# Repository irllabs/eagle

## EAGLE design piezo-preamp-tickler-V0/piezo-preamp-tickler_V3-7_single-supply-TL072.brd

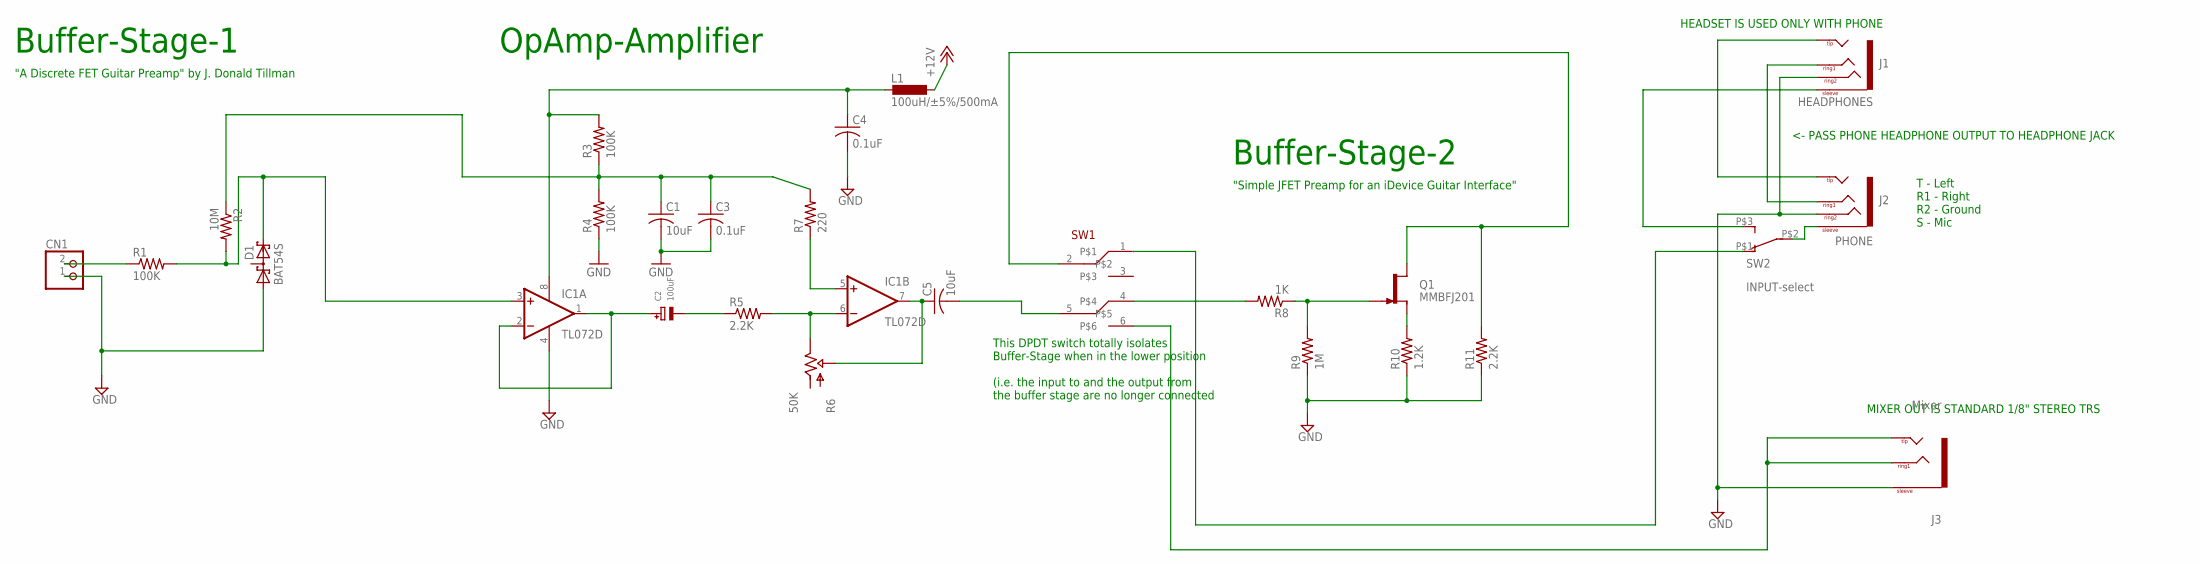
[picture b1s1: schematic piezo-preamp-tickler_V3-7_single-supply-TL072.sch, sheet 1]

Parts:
C1: 10uF; C0805K
C2: 100uF; EIA7343-31/D-R
C3, C4: 0.1uF; C0805K
C5: 10uF; C0805
CN1: JST_2PIN-THM; JST-PH-2-THM
D1: BAT54S; SOT23
IC1: TL072D; SO08
J1: HEADPHONES; TRRS_SJ-43514-SMT-TR
J2: PHONE; TRRS_SJ-43514-SMT-TR
J3: Mixer; TRS_SJ-3524-SMT
L1: 100uH/±5%/500mA; L3225M
Q1: MMBFJ201; SOT23-3
R1, R3, R4: 100K; R0603
R2: 10M; R0603
R5, R11: 2.2K; R0603
R6: 50K; THUMBPOT14MM
R7: 220; R0603
R8: 1K; R0603
R9: 1M; R0603
R10: 1.2K; R0603
SW1: SWITCH_DPDT; SWITCH_DPDT_CL-SB-22B
SW2: INPUT-select; SWITCH_SPDT_CL-SB-12B

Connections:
+12V: L1.1; also elsewhere on the board
GND: C1.2, C3.2, C4.2, CN1.1 (2), D1.1 (A1), IC1.4 (V-), J1.RING2, J2.RING2, J3.1 (SLEEVE), R4.1, R9.1, R10.1, R11.1; also elsewhere on the board
unnamed: D1.2 (C2), IC1.3 (+IN), R1.2, R2.2
unnamed: CN1.2 (1), R1.1
unnamed: Q1.2 (S), R10.2
unnamed: J1.EARTH (SLEEVE), SW2.P$3 (3)
unnamed: IC1.5 (+IN), R7.1
unnamed: C5.1, C5.+, IC1.7 (OUT), R6.P$2 (WIPER)
unnamed: IC1.6 (-IN), R5.2, R6.P$3 (OUT)
unnamed: C4.1, IC1.8 (V+), L1.2, R3.2
unnamed: C1.1, C3.1, R2.1, R3.1, R4.2, R7.2
unnamed: Q1.3 (G), R8.1, R9.2
unnamed: R8.2, SW1.4
unnamed: J3.2 (TIP), J3.3 (RING1), J3.4 (TIP), SW1.6
unnamed: J1.RING1, J2.RING1
unnamed: C2.-, R5.1
unnamed: C5.2, C5.-, SW1.5
unnamed: J2.EARTH (SLEEVE), SW2.P$2 (2)
unnamed: SW1.1, SW2.P$1 (1)
unnamed: C2.+, IC1.1 (OUT), IC1.2 (-IN)
unnamed: J1.TIP, J2.TIP
SELECT: Q1.1 (D), R11.2, SW1.2

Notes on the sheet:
Buffer-Stage-1
OpAmp-Amplifier
Buffer-Stage-2
"A Discrete FET Guitar Preamp" by J. Donald Tillman
"Simple JFET Preamp for an iDevice Guitar Interface"
T - Left R1 - Right R2 - Ground S - Mic
HEADSET IS USED ONLY WITH PHONE
MIXER OUT IS STANDARD 1/8" STEREO TRS
<- PASS PHONE HEADPHONE OUTPUT TO HEADPHONE JACK
This DPDT switch totally isolates Buffer-Stage when in the lower position (i.e. the input to and the output from the buffer stage are no longer connected

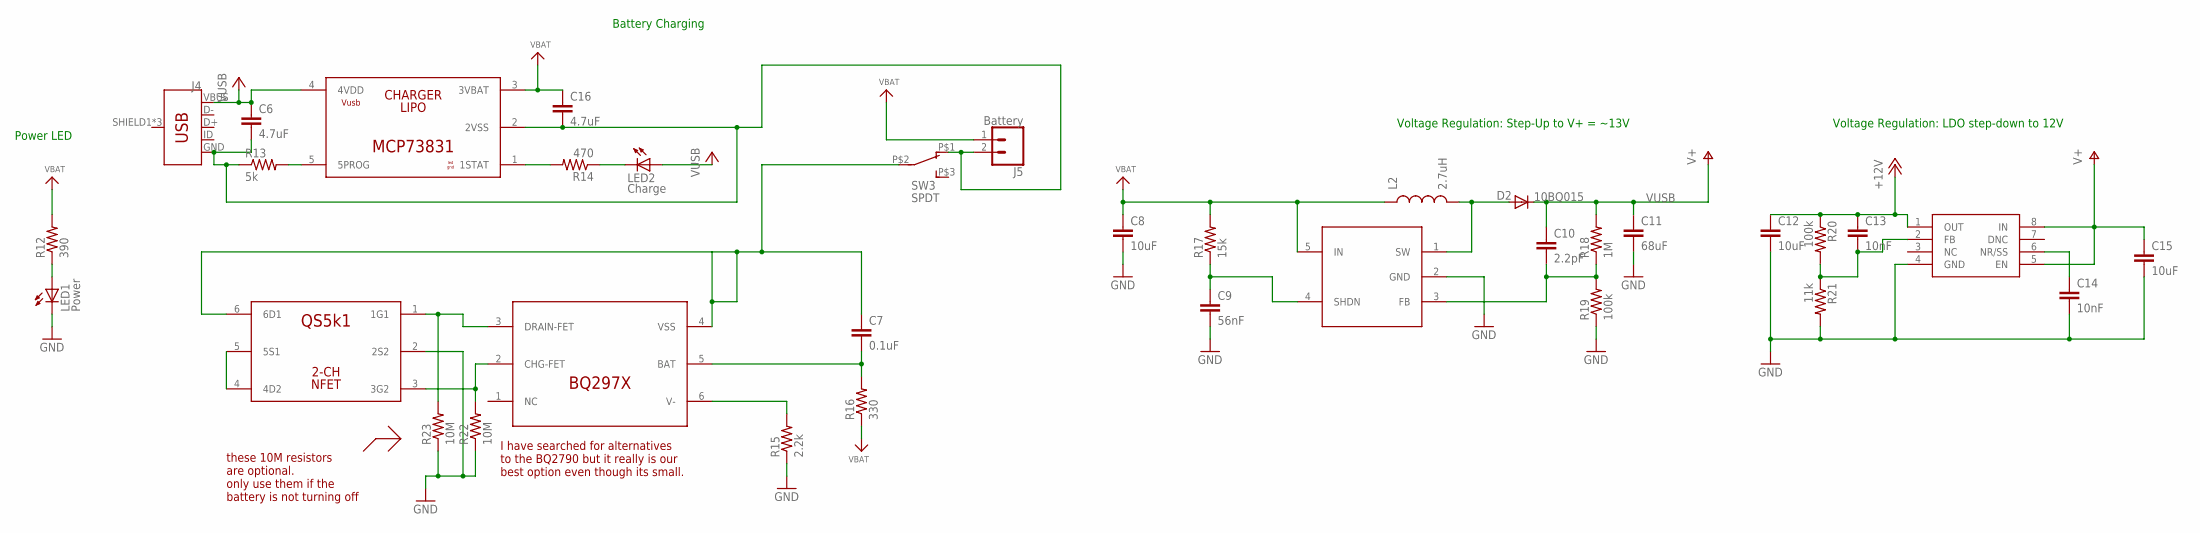
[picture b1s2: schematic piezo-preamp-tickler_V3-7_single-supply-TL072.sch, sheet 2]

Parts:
C6, C16: 4.7uF; C0603
C7: 0.1uF; C0603
C8, C12, C15: 10uF; C0603
C9: 56nF; C0603
C10: 2.2pF; C0603
C11: 68uF; C1206
C13, C14: 10nF; C0603
D2: 10BQ015; SMA-DIODE
IC2: MCP73831; SOT-23-5
IC3: QS6K1; SOT457R_PHILIPS
IC4: BQ297X; WSON-6-LONG
IC5: SC4503; SOT23-5
IC6: TPS7A49; MSOP-8
J4: USB_MICRO-BREDUCED_PASTE; USB-B-MICRO-SMD_RED_PASTE
J5: Battery; 1X02_LOCK
L2: 2.7uH; CR54
LED1: Power; LED3MM
LED2: Charge; LED3MM
R12: 390; R0603
R13: 5k; R0603
R14: 470; R0603
R15: 2.2k; R0603
R16: 330; R0603
R17: 15k; R0603
R18: 1M; R0603
R19, R20: 100k; R0603
R21: 11k; R0603
R22, R23: 10M; R0603
SW3: SPDT; SWITCH_SPDT_CL-SB-12B

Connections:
+5V: C6.1, IC2.4 (4VDD), J4.VBUS, LED2.A
+12V: C12.1, C13.1, IC6.1 (OUT), R20.1; also elsewhere on the board
BATGND: C7.1, IC3.6 (6D1), IC4.4 (VSS), SW3.P$2 (2)
GND: C8.2, C9.2, C11.2, C12.2, C14.2, C15.2, IC3.2 (2S2), IC5.2 (GND), IC6.4 (GND), LED1.K (C), R15.1, R19.1, R21.2, R22.1, R23.1; also elsewhere on the board
unnamed: LED1.A, R12.1
unnamed: IC2.5 (5PROG), R13.2
unnamed: LED2.K (C), R14.1
unnamed: IC3.4 (4D2), IC3.5 (5S1)
unnamed: IC2.1 (1STAT), R14.2
unnamed: C13.2, IC6.2 (FB), R20.2, R21.1
unnamed: IC3.1 (1G1), IC4.3 (DRAIN-FET), R23.2
unnamed: C14.1, IC6.6 (NR/SS)
unnamed: C9.1, IC5.4 (SHDN), R17.1
unnamed: C10.2, IC5.3 (FB), R18.1, R19.2
unnamed: IC3.3 (3G2), IC4.2 (CHG-FET), R22.2
unnamed: D2.A, IC5.1 (SW), L2.P$2 (2)
unnamed: IC4.6 (V-), R15.2
unnamed: C7.2, IC4.5 (BAT), R16.2
USBGND: C6.2, C16.2, IC2.2 (2VSS), J4.GND, J5.2, R13.1, SW3.P$1 (1)
VBAT: C8.1, C16.1, IC2.3 (3VBAT), IC5.5 (IN), J5.1, L2.P$1 (1), R12.2, R16.1, R17.2
VUSB: C10.1, C11.1, C15.1, D2.C, IC6.5 (EN), IC6.8 (IN), R18.2

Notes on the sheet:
Voltage Regulation: Step-Up to V+ = ~13V
Power LED
Voltage Regulation: LDO step-down to 12V
Battery Charging
I have searched for alternatives to the BQ2790 but it really is our best option even though its small.
these 10M resistors are optional. only use them if the battery is not turning off

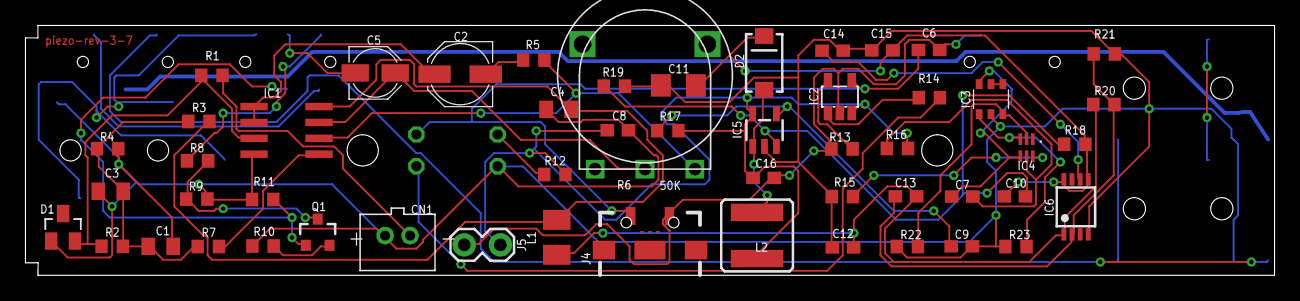
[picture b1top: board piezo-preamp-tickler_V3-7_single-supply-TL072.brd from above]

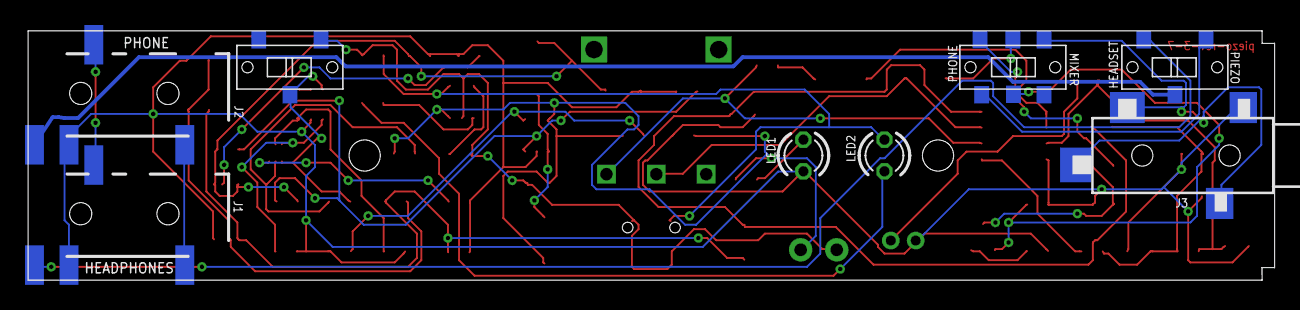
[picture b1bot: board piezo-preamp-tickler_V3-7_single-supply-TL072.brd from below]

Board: 2 copper layers, 100.0 x 20.0 mm, 61 parts (8 on the bottom side), 41 nets.

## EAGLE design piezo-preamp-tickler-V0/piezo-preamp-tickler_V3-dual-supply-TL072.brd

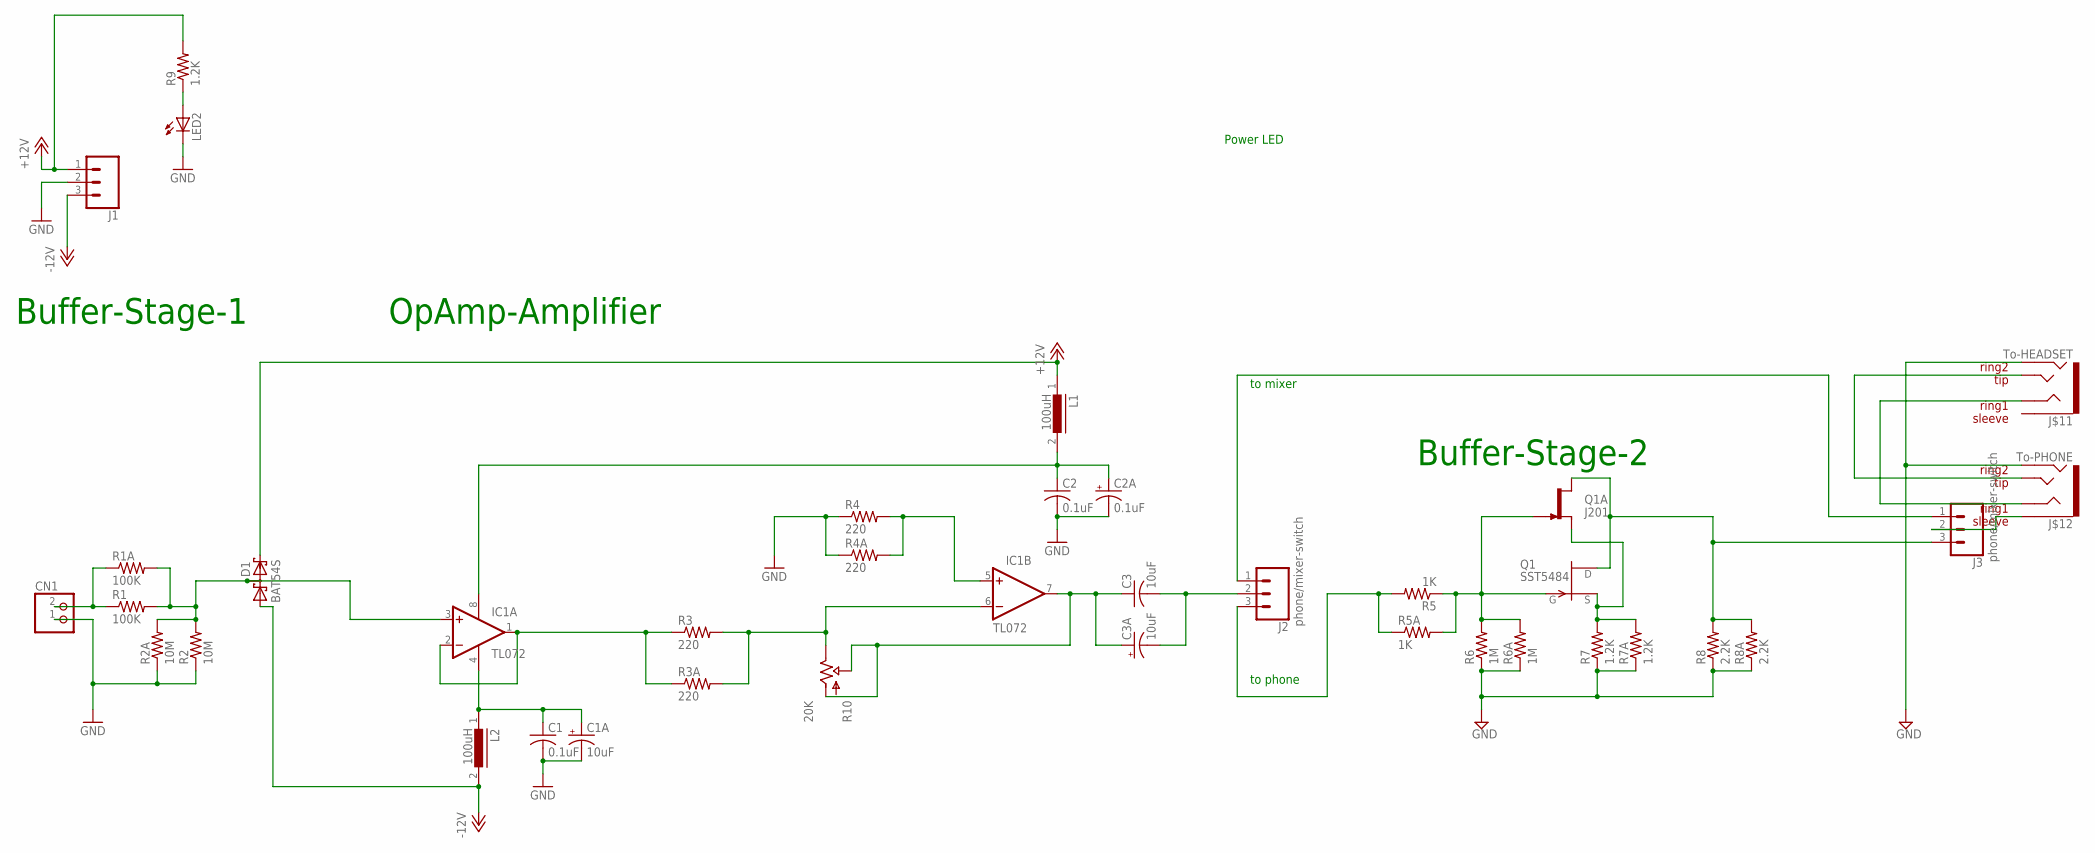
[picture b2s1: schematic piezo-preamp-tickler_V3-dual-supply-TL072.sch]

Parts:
C1, C2: 0.1uF; C0805K
C1A, C3A: 10uF; E2,5-6E
C2A: 0.1uF; E2,5-6E
C3: 10uF; C0805K
CN1: JST_2PIN-THM; JST-PH-2-THM
D1: BAT54S; SOT23
IC1: TL072; SO08
J1: CONN_03LOCK; 1X03_LOCK
J2, J3: phone/mixer-switch; 1X03_LOCK
J$11: To-HEADSET; TRRS-SJ-43514-SMT-TR
J$12: To-PHONE; TRRS-SJ-43514-SMT-TR
L1, L2: 100uH; LBC-SE
LED2: LED3MM
Q1: SST5484; SOT23
Q1A: J201; TO92-
R1: 100K; R0603
R1A: 100K; 0204V
R2: 10M; R0603
R2A: 10M; 0204V
R3, R4: 220; R0603
R3A, R4A: 220; 0204V
R5: 1K; R0603
R5A: 1K; 0204V
R6: 1M; R0603
R6A: 1M; 0204V
R7: 1.2K; R0603
R7A, R9: 1.2K; 0204V
R8: 2.2K; R0603
R8A: 2.2K; 0204V
R10: 20K; TRIMPOT-MULTI

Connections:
+12V: D1.2 (C2), J1.1, L1.1, R9.2
-12V: D1.1 (A1), J1.3, L2.2
GND: C1.2, C1A.-, C2.2, C2A.-, CN1.1 (2), J1.2, J$11.4 (RING2), J$12.4 (RING2), LED2.K (C), R2.1, R2A.1, R4.1, R4A.1, R6.1, R6A.1, R7.1, R7A.1, R8.1, R8A.1
unnamed: IC1.1 (OUT), IC1.2 (-IN), R3.1, R3A.1
unnamed: J2.3, R5.2, R5A.1
unnamed: C1.1, C1A.+, IC1.4 (V-), L2.1
unnamed: LED2.A, R9.1
unnamed: IC1.5 (+IN), R4.2, R4A.2
unnamed: IC1.6 (-IN), R3.2, R3A.2, R10.P$1 (OUT), R10.P$3 (OUT), R10.P$4 (OUT), R10.P$6 (OUT), R10.P$9 (OUT)
unnamed: C3.2, C3A.-, J2.2
unnamed: CN1.2 (1), R1.1, R1A.1
unnamed: Q1.2 (S), Q1A.2 (S), R7.2, R7A.2
unnamed: C3.1, C3A.+, IC1.7 (OUT), R10.P$10 (WIPER), R10.P$12 (WIPER), R10.P$13 (WIPER), R10.P$15 (WIPER), R10.P$16 (WIPER), R10.P$18 (WIPER), R10.P$20 (IN), R10.P$21 (IN), R10.P$22 (IN), R10.P$24 (IN), R10.P$27 (IN)
unnamed: C2.1, C2A.+, IC1.8 (V+), L1.2
unnamed: D1.3 (C1A2), IC1.3 (+IN), R1.2, R1A.2, R2.2, R2A.2
unnamed: Q1.3 (G), Q1A.1 (G), R5.1, R5A.2, R6.2, R6A.2
unnamed: J2.1, J3.1
unnamed: J$11.2 (TIP), J$12.2 (TIP)
unnamed: J$11.3 (RING1), J$12.3 (RING1)
unnamed: J3.2, J$12.1 (EARTH)
SELECT1: J3.3, Q1.1 (D), Q1A.3 (D), R8.2, R8A.2

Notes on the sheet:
Buffer-Stage-1
OpAmp-Amplifier
Buffer-Stage-2
to mixer
to phone
Power LED

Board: 2 copper layers, 37 parts (0 on the bottom side), 21 nets, no tracks yet.

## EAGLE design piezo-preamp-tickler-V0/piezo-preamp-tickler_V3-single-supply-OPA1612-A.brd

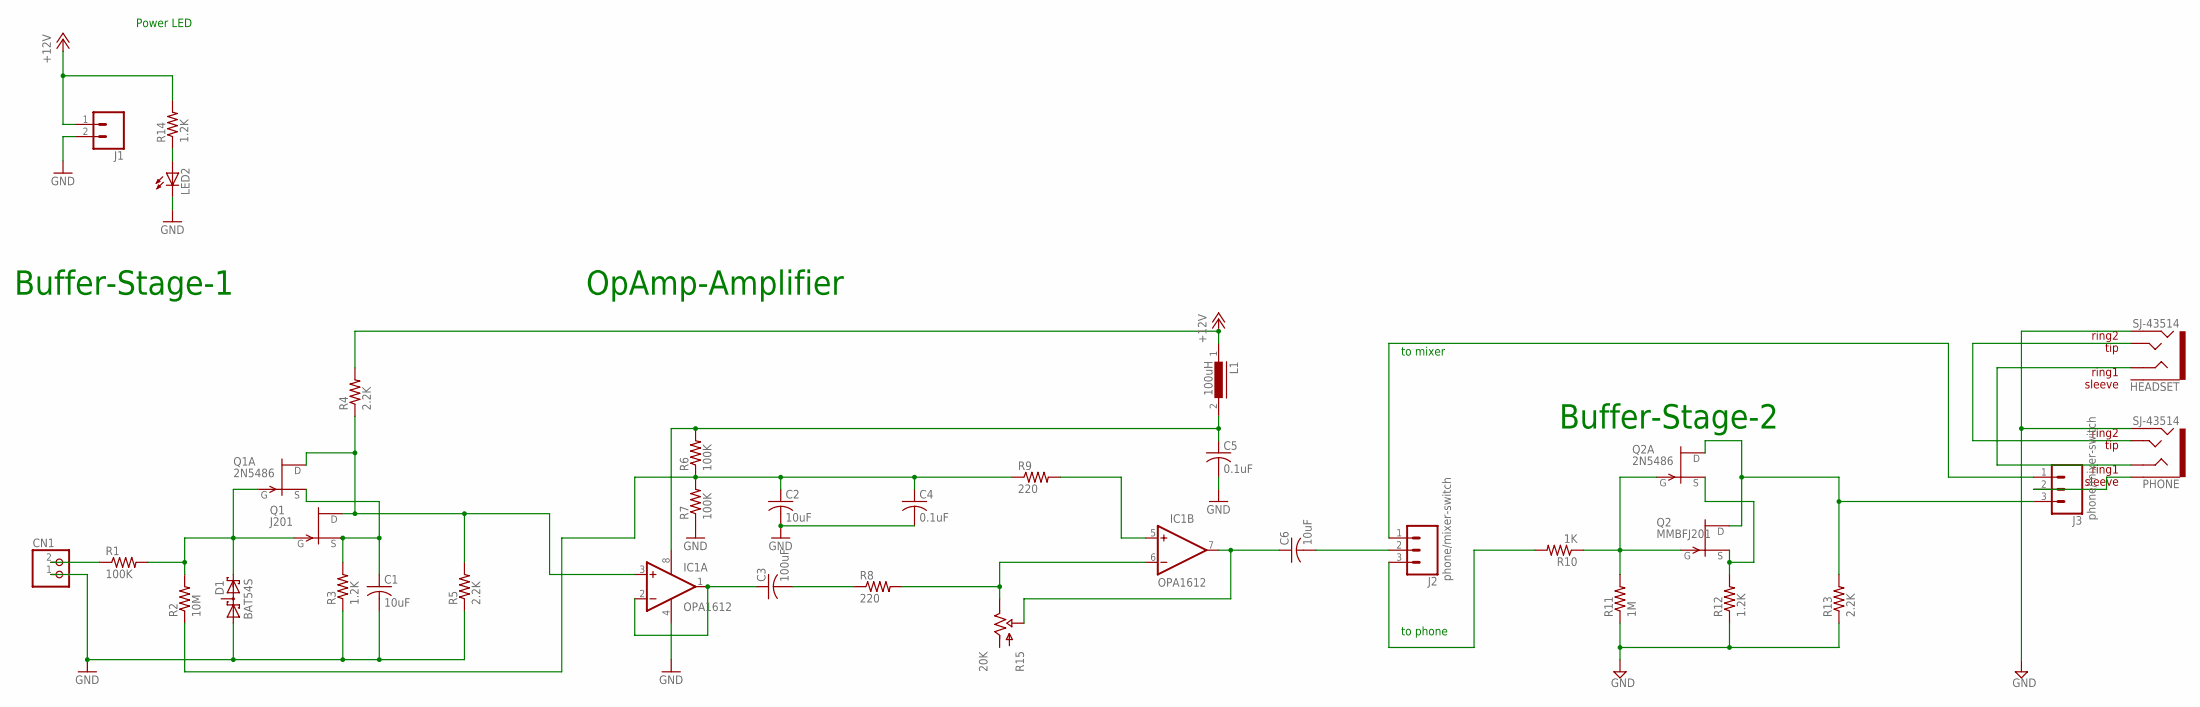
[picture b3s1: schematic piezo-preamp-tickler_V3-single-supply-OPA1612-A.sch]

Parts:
C1, C2, C6: 10uF; C1206
C3: 100uF; C1206
C4, C5: 0.1uF; C0805K
CN1: JST_2PIN-THM; JST-PH-2-THM
D1: BAT54S; SOT23
HEADSET: SJ-43514; TRRS_SJ-43514-SMT-TR
IC1: OPA1612; SO08
J1: CONN_02LOCK; 1X02_LOCK
J2, J3: phone/mixer-switch; 1X03_LOCK
L1: 100uH; LBC-SE
LED2: LED3MM
PHONE: SJ-43514; TRRS_SJ-43514-SMT-TR
Q1: J201; SOT23
Q1A, Q2A: 2N5486; TO92-
Q2: MMBFJ201; SOT23
R1, R6, R7: 100K; R0603
R2: 10M; R0603
R3, R12: 1.2K; R0603
R4, R5, R13: 2.2K; R0603
R8, R9: 220; R0603
R10: 1K; R0603
R11: 1M; R0603
R14: 1.2K; 0204V
R15: 20K; TRIMPOT-MULTI

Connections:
+12V: J1.1, L1.1, R4.2, R14.2
DRAINE1: IC1.3 (+IN), Q1.1 (D), Q1A.3 (D), R4.1, R5.2
GATE1: D1.2 (C2), Q1.3 (G), Q1A.1 (G), R1.2, R2.2
GATE2: Q2.3 (G), Q2A.1 (G), R10.1, R11.2
GND: C1.2, C2.2, C4.2, C5.2, CN1.1 (2), D1.1 (A1), HEADSET.RING2, IC1.4 (V-), J1.2, LED2.K (C), PHONE.RING2, R3.1, R5.1, R7.1, R11.1, R12.1, R13.1
unnamed: C3.1, IC1.1 (OUT), IC1.2 (-IN)
unnamed: LED2.A, R14.1
unnamed: J2.3, R10.2
unnamed: IC1.5 (+IN), R9.2
unnamed: IC1.6 (-IN), R8.2, R15.P$1 (OUT), R15.P$3 (OUT), R15.P$4 (OUT), R15.P$6 (OUT), R15.P$9 (OUT)
unnamed: C6.2, J2.2
unnamed: CN1.2 (1), R1.1
unnamed: C6.1, IC1.7 (OUT), R15.P$10 (WIPER), R15.P$12 (WIPER), R15.P$13 (WIPER), R15.P$15 (WIPER), R15.P$16 (WIPER), R15.P$18 (WIPER)
unnamed: C5.1, IC1.8 (V+), L1.2, R6.2
unnamed: C2.1, C4.1, R2.1, R6.1, R7.2, R9.1
unnamed: J2.1, J3.1
unnamed: HEADSET.TIP, PHONE.TIP
unnamed: HEADSET.RING1, PHONE.RING1
unnamed: J3.2, PHONE.EARTH
unnamed: C3.2, R8.1
NAME: J3.3, Q2.1 (D), Q2A.3 (D), R13.2
SOURCE: Q2.2 (S), Q2A.2 (S), R12.2
SOURCE1: C1.1, Q1.2 (S), Q1A.2 (S), R3.2

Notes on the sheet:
Buffer-Stage-1
OpAmp-Amplifier
Buffer-Stage-2
to mixer
to phone
Power LED

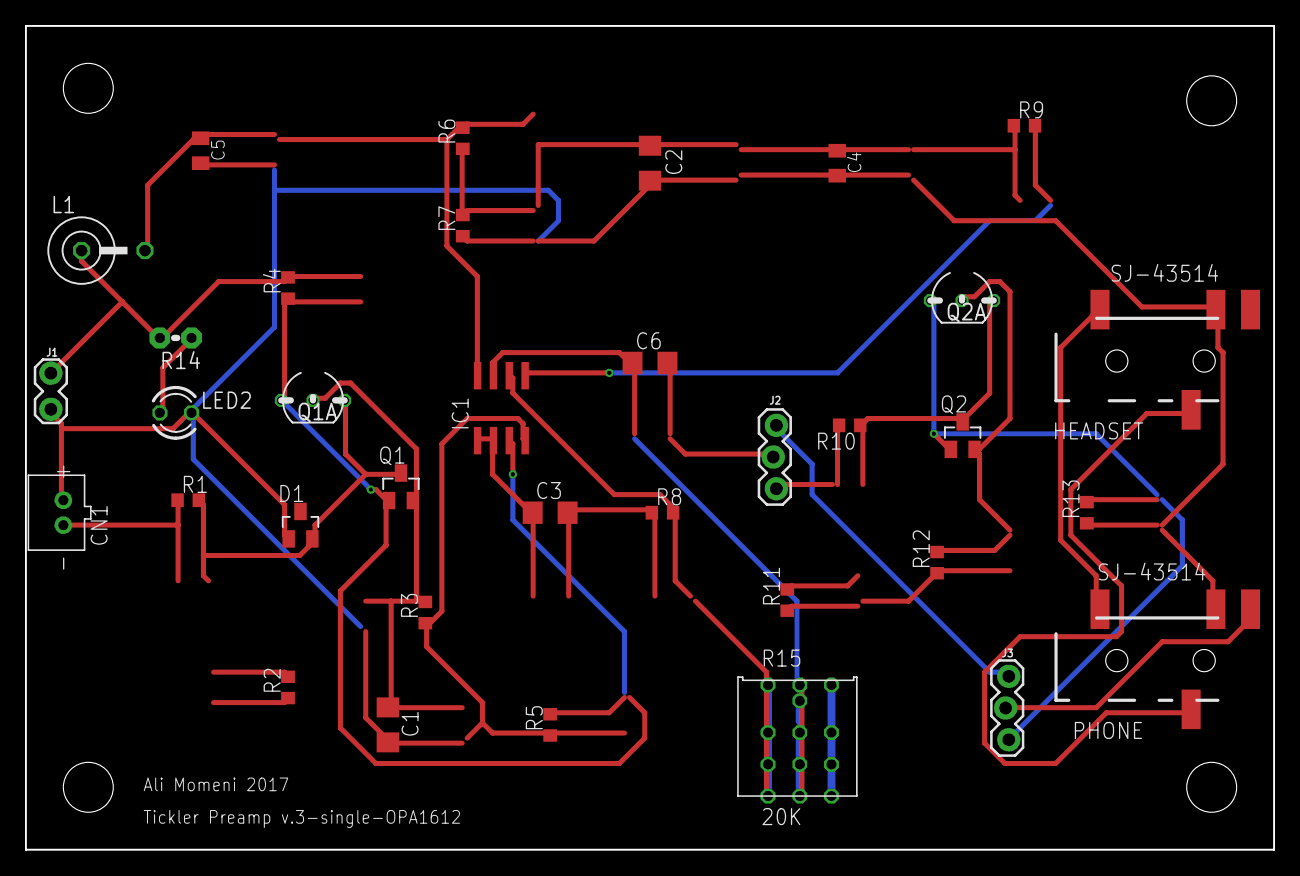
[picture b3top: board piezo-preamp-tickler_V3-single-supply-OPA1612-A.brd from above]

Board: 2 copper layers, 100.0 x 66.0 mm, 35 parts (0 on the bottom side), 23 nets.

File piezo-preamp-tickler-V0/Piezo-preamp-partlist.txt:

Partlist

Exported from piezo-preamp-tickler_V3-2_single-supply-OPA1642.sch at 12/20/2017 9:03 PM

"EAGLE Version 8.5.1 Copyright (c) 1988-2017 Autodesk, Inc."

Assembly variant: 

Part       Value          Device                    Package               Library             Sheet

C2         10uF           C-USC1206                 C1206                 rcl                 1
C3         100uF          CAP_TANTALUMD/7343_REFLOW EIA7343-31/D-R        microbuilder        1
C4         0.1uF          C-USC0805K                C0805K                adafruit            1
C5         0.1uF          C-USC0805K                C0805K                adafruit            1
C6         10uF           C-USC1206                 C1206                 adafruit            1
CN1                       JST_2PIN-THM              JST-PH-2-THM          adafruit            1
D1         1N4148W        ZENER-DIOD                SOD123                CMU-ArtFab          1
D2         1N4148W        ZENER-DIOD                SOD123                CMU-ArtFab          1
HEADSET    SJ-43514       TRRS-3.5MMLGPADS          TRRS_SJ-43514-SMT-TR  CMU-ArtFab          1
IC1        OPA1612        OPA2134UA                 SO08                  linear              1
J1                        CONN_02LOCK               1X02_LOCK             SparkFun-Connectors 1
L1         100uH          L-USL3225P                L3225P                rcl                 1
LED1                      LED3MM                    LED3MM                led                 1
"MIXER-OUT  TRS-1/8""-3.5MM TRS-1/8""-3.5MM            TRS_SJ-3524-SMT       CMU-ArtFab          1"
PHONE      SJ-43514       TRRS-3.5MMLGPADS          TRRS_SJ-43514-SMT-TR  CMU-ArtFab          1
Q2         MMBFJ201       SST5484                   SOT23                 transistor-fet      1
R1         100K           R-US_R0603                R0603                 CMU-ArtFab          1
R2         10M            R-US_R0603                R0603                 CMU-ArtFab          1
R6         100K           R-US_R0603                R0603                 CMU-ArtFab          1
R7         100K           R-US_R0603                R0603                 CMU-ArtFab          1
R8         220            R-US_R0603                R0603                 CMU-ArtFab          1
R9         220            R-US_R0603                R0603                 CMU-ArtFab          1
R10        1K             R-US_R0603                R0603                 CMU-ArtFab          1
R11        1M             R-US_R0603                R0603                 CMU-ArtFab          1
R12        1.2K           R-US_R0603                R0603                 CMU-ArtFab          1
R13        2.2K           R-US_R0603                R0603                 CMU-ArtFab          1
R14        1.2K           R-US_R0603                R0603                 CMU-ArtFab          1
R15        20K            POTTRIMPOT-MULTI          TRIMPOT-MULTI         CMU-ArtFab          1
SW1-INPUT  SPDTCSS-1210B  SWITCH_SPDTCSS-1210B      SWITCH_SPDT_CSS-1210B CMU-ArtFab          1
SW1-OUTPUT SWITCH_DPDT    SWITCH_DPDT               SWITCH_DPDT_CL-SB-22B CMU-ArtFab          1

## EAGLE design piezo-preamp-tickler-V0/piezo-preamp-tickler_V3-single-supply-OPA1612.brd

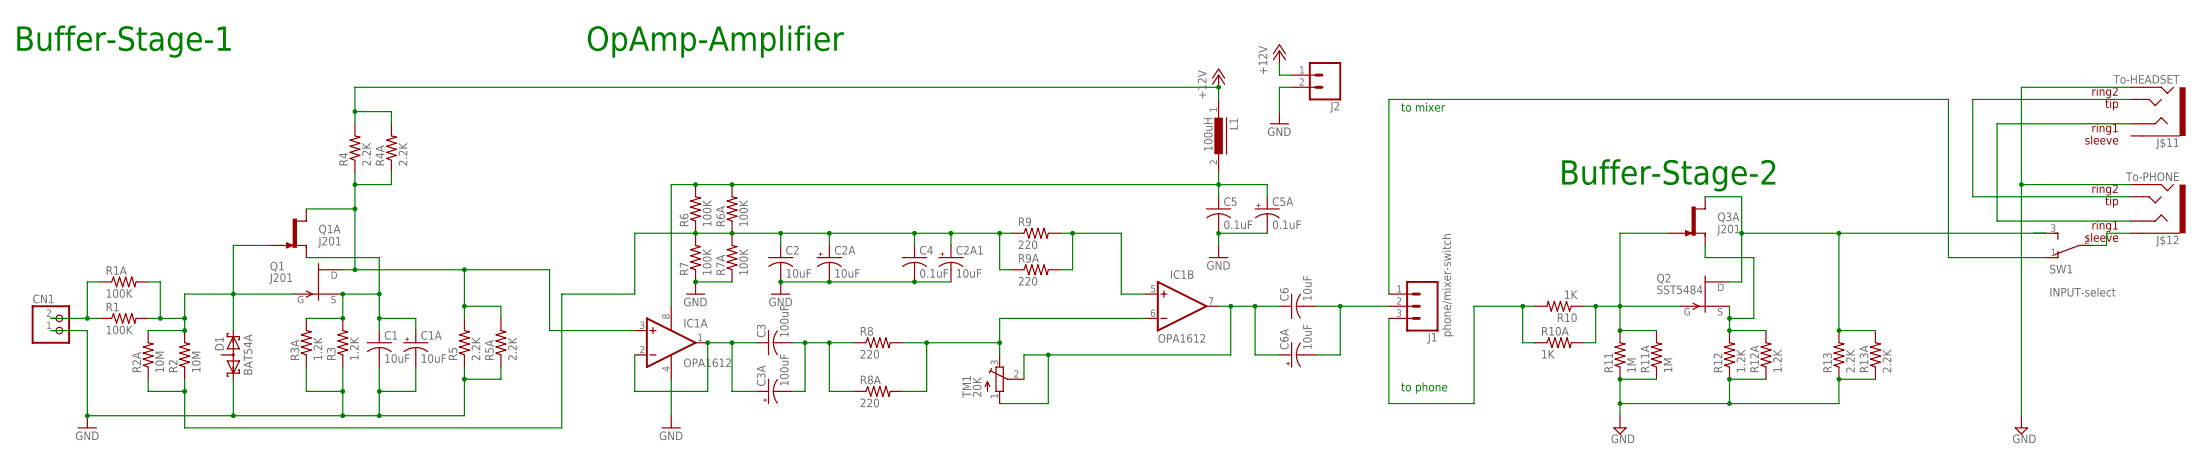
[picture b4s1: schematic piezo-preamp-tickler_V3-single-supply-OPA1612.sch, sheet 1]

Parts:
C1, C2, C6: 10uF; C0805K
C1A, C2A, C2A1, C6A: 10uF; E2,5-6E
C3: 100uF; C0805K
C3A: 100uF; E2,5-6E
C4, C5: 0.1uF; C0805K
C5A: 0.1uF; E2,5-6E
CN1: JST_2PIN-THM; JST-PH-2-THM
D1: BAT54A; SOT23
IC1: OPA1612; SO08
J1: phone/mixer-switch; 1X03_LOCK
J2: CONN_02LOCK; 1X02_LOCK
J$11: To-HEADSET; TRRS-SJ-43514-SMT-TR
J$12: To-PHONE; TRRS-SJ-43514-SMT-TR
L1: 100uH; LBC-SE
Q1: J201; SOT23
Q1A, Q3A: J201; TO92-
Q2: SST5484; SOT23
R1, R6, R7: 100K; R0603
R1A, R6A, R7A: 100K; 0204V
R2: 10M; R0603
R2A: 10M; 0204V
R3, R12: 1.2K; R0603
R3A, R12A: 1.2K; 0204V
R4, R5, R13: 2.2K; R0603
R4A, R5A, R13A: 2.2K; 0204V
R8, R8A, R9: 220; R0603
R9A: 220; 0204V
R10: 1K; R0603
R10A: 1K; 0204V
R11: 1M; R0603
R11A: 1M; 0204V
SW1: INPUT-select; SWITCH_SPDT-TE-CONNECT
TM1: 20K; TC33X

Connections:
+12V: J2.1, L1.1, R4.2, R4A.2
GND: C1.2, C1A.-, C2.2, C2A.-, C2A1.-, C4.2, C5.2, C5A.-, CN1.1 (2), D1.1 (K1), IC1.4 (V-), J2.2, J$11.4 (RING2), J$12.4 (RING2), R3.1, R3A.1, R5.1, R5A.1, R7.1, R7A.1, R11.1, R11A.1, R12.1, R12A.1, R13.1, R13A.1; also elsewhere on the board
unnamed: C3.1, C3A.+, IC1.1 (OUT), IC1.2 (-IN)
unnamed: J1.3, R10.2, R10A.1
unnamed: IC1.5 (+IN), R9.2, R9A.2
unnamed: IC1.6 (-IN), R8.2, R8A.2, TM1.3 (E)
unnamed: C6.2, C6A.-, J1.2
unnamed: CN1.2 (1), R1.1, R1A.1
unnamed: IC1.3 (+IN), Q1.1 (D), Q1A.3 (D), R4.1, R4A.1, R5.2, R5A.2
unnamed: Q2.2 (S), Q3A.2 (S), R12.2, R12A.2
unnamed: C6.1, C6A.+, IC1.7 (OUT), TM1.1 (A), TM1.2 (S)
unnamed: C5.1, C5A.+, IC1.8 (V+), L1.2, R6.2, R6A.2
unnamed: C1.1, C1A.+, Q1.2 (S), Q1A.2 (S), R3.2, R3A.2
unnamed: C2.1, C2A.+, C2A1.+, C4.1, R2.1, R2A.1, R6.1, R6A.1, R7.2, R7A.2, R9.1, R9A.1
unnamed: D1.2 (K2), Q1.3 (G), Q1A.1 (G), R1.2, R1A.2, R2.2, R2A.2
unnamed: Q2.3 (G), Q3A.1 (G), R10.1, R10A.2, R11.2, R11A.2
unnamed: J1.1, SW1.1
unnamed: J$11.2 (TIP), J$12.2 (TIP)
unnamed: J$11.3 (RING1), J$12.3 (RING1)
unnamed: J$12.1 (EARTH), SW1.2
unnamed: C3.2, C3A.-, R8.1, R8A.1
SELECT1: Q2.1 (D), Q3A.3 (D), R13.2, R13A.2, SW1.3

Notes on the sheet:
Buffer-Stage-1
OpAmp-Amplifier
Buffer-Stage-2
to mixer
to phone

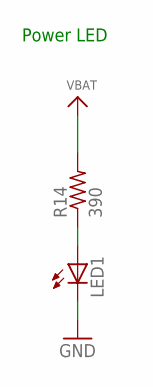
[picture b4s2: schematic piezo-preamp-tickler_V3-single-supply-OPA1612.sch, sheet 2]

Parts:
LED1: LED3MM
R14: 390; R0805

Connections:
GND: LED1.K (C); also elsewhere on the board
unnamed: LED1.A, R14.1
VBAT: R14.2

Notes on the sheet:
Power LED

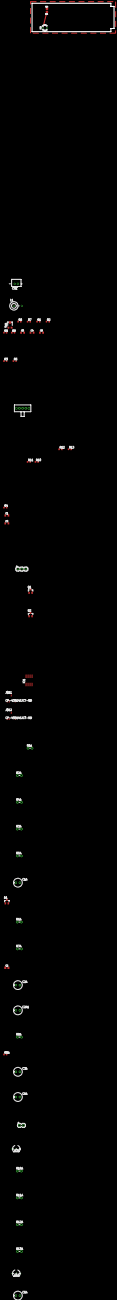
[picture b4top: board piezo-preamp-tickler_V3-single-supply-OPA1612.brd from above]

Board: 2 copper layers, 52.0 x 18.0 mm, 54 parts (0 on the bottom side), 23 nets.

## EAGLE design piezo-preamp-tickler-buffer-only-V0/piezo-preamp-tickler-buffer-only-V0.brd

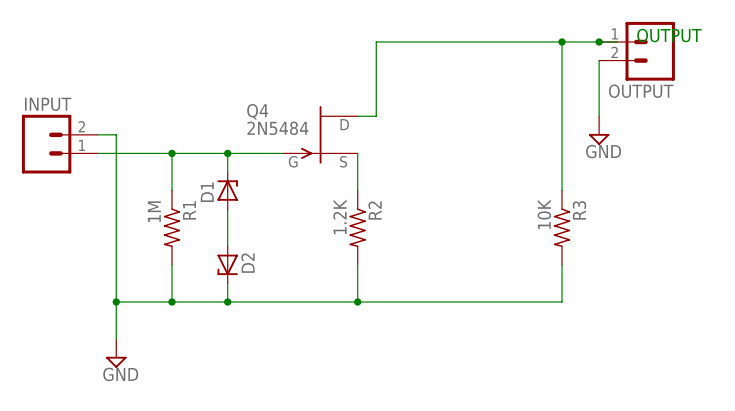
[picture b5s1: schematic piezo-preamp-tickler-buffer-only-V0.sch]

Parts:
D1, D2: 1N821; DO35Z10
INPUT: M02LOCK; 1X02_LOCK
OUTPUT: M02LOCK; 1X02_LOCK
Q4: 2N5484; TO92-
R1: 1M; VMTA55
R2: 1.2K; VMTA55
R3: 10K; VMTA55

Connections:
GND: D2.C, INPUT.2, OUTPUT.2, R1.2, R2.2, R3.2
JFET-GATE: D1.C, INPUT.1, Q4.1 (G), R1.1
unnamed: D1.A, D2.A
unnamed: OUTPUT.1, Q4.3 (D), R3.1
unnamed: Q4.2 (S), R2.1

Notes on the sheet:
OUTPUT

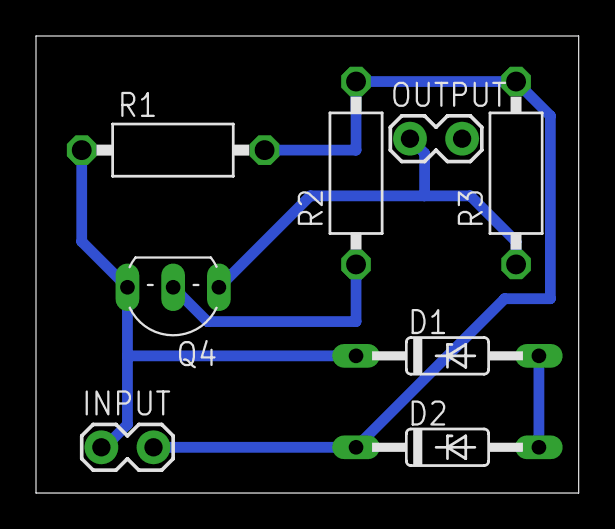
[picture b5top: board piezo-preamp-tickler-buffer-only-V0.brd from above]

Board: 2 copper layers, 30.1 x 25.4 mm, 8 parts (0 on the bottom side), 5 nets.

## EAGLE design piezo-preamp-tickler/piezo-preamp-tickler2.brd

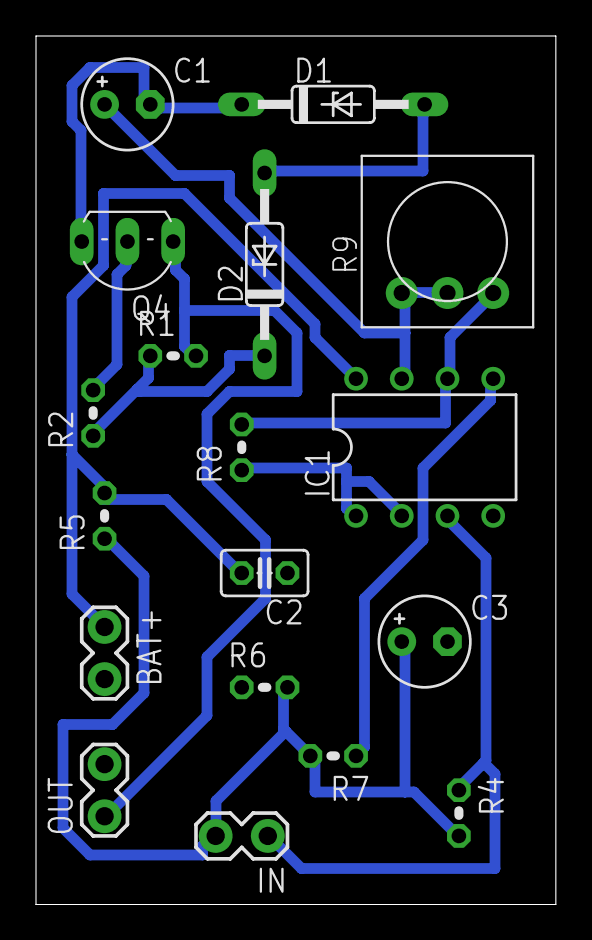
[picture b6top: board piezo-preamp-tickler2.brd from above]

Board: 2 copper layers, 28.9 x 48.2 mm, 18 parts (0 on the bottom side), 13 nets.

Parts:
BAT+: 1X02_LOCK
C1, C3: 10u; E2,5-5
C2: 100n; C025-025X050
D1, D2: DO35Z10
IC1: TLC272; DIL08
IN: 1X02_LOCK
OUT: 1X02_LOCK
Q4: 2N5484; TO92-
R1: 10K; 0204V
R2: 1.2K; 0204V
R4: 10k..10m; 0204V
R5: 150K; 0204V
R6: 100K; 0204V
R7, R8: 1K; 0204V
R9: TRIM-3386

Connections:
GND: BAT+.2, C2.1, C3.-, IC1.4, OUT.2, R6.1
unnamed: D1.A, D2.A
unnamed: OUT.1, Q4.3, R1.2
unnamed: Q4.2, R2.2
unnamed: IC1.5, R7.1
unnamed: C1.+, IC1.7, R9.1, R9.2
unnamed: IC1.6, R8.2, R9.3
unnamed: C3.+, IN.2, R4.2, R5.1, R6.2, R7.2
unnamed: IC1.3, IN.1, R4.1
unnamed: C1.-, D1.C, Q4.1
unnamed: IC1.1, IC1.2, R8.1
R3: D2.C, R1.1, R2.1
V9V: BAT+.1, C2.2, IC1.8, R5.2

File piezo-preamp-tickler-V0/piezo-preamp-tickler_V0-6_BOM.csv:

"Part";"Value";"Device";"Package";"Description";"";
"BAT1";"";"BATTERYA23";"BATTERY-A23";"Battery Holders";"";
"C1";"10u";"CPOL-EUE2.5-5";"E2,5-5";"POLARIZED CAPACITOR, European symbol";"";
"C2";"100n";"C-EU025-025X050";"C025-025X050";"CAPACITOR, European symbol";"";
"C3";"10u";"CPOL-EUE2.5-5";"E2,5-5";"POLARIZED CAPACITOR, European symbol";"";
"D1";"";"1N821";"DO35Z10";"Reference DIODE";"";
"D2";"";"1N821";"DO35Z10";"Reference DIODE";"";
"IC1";"TLC272";"TLC272P";"DIL08";"OP AMP";"";
"IN";"";"M02LOCK";"1X02_LOCK";"Header 2";"";
"INPUT-SELECT";"";"M03LOCK";"1X03_LOCK";"Header 3";"";
"Q4";"2N5484";"2N5484";"TO92-";"N-Channel JFETs";"";
"R1";"10K";"R-US_0204/2V";"0204V";"RESISTOR, American symbol";"";
"R2";"1.2K";"R-US_0204/2V";"0204V";"RESISTOR, American symbol";"";
"R3";"1M";"R-US_0204/2V";"0204V";"RESISTOR, American symbol";"";
"R4";"10K";"R-US_0204/2V";"0204V";"RESISTOR, American symbol";"";
"R5";"150K";"R-US_0204/2V";"0204V";"RESISTOR, American symbol";"";
"R6";"100K";"R-US_0204/2V";"0204V";"RESISTOR, American symbol";"";
"R7";"1K";"R-US_0204/2V";"0204V";"RESISTOR, American symbol";"";
"R8";"1K";"R-US_0204/2V";"0204V";"RESISTOR, American symbol";"";
"R9";"";"TRIMPOT3386";"TRIM-3386";"SMT trimmer potentiometer part number TC33X";"";
"R10";"1K";"R-US_0204/2V";"0204V";"RESISTOR, American symbol";"";
"TO-HEADSET";"AUDIO-JACK3";"AUDIO-JACK3";"AUDIO-JACK-TRRS-SMD";"Audio jack - 3.5mm TRRS variety - two rings.";"";
"TO-PHONE";"AUDIO-JACK3";"AUDIO-JACK3";"AUDIO-JACK-TRRS-SMD";"Audio jack - 3.5mm TRRS variety - two rings.";"";

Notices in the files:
parts and their libraries:
SparkFun-Connectors: Licensing: Creative Commons ShareAlike 4.0 International - https://creativecommons.org/licenses/by-sa/4.0
microbuilder: This work is placed in the public domain, and may be freely used for commercial and non-commercial work with the following conditions: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
